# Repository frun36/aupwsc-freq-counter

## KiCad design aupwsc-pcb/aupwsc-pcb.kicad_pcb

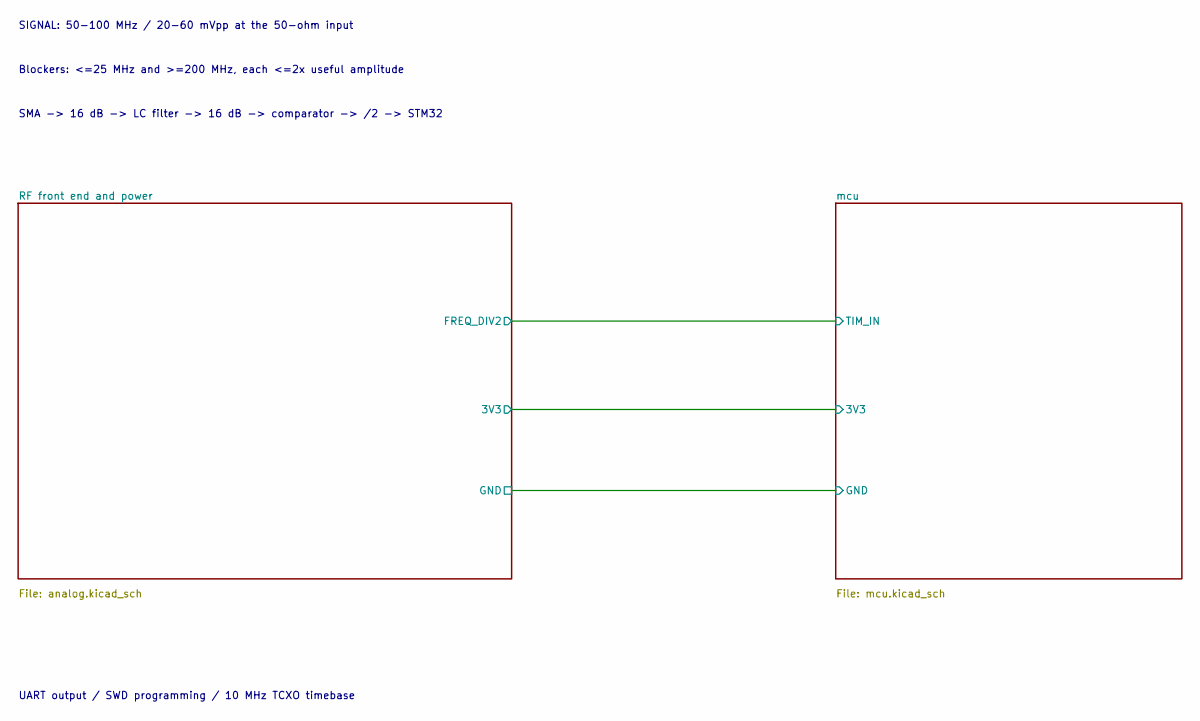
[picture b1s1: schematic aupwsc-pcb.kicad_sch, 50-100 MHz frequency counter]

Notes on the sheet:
UART output / SWD programming / 10 MHz TCXO timebase
SIGNAL: 50-100 MHz / 20-60 mVpp at the 50-ohm input
SMA -> 16 dB -> LC filter -> 16 dB -> comparator -> /2 -> STM32
Blockers: <=25 MHz and >=200 MHz, each <=2x useful amplitude

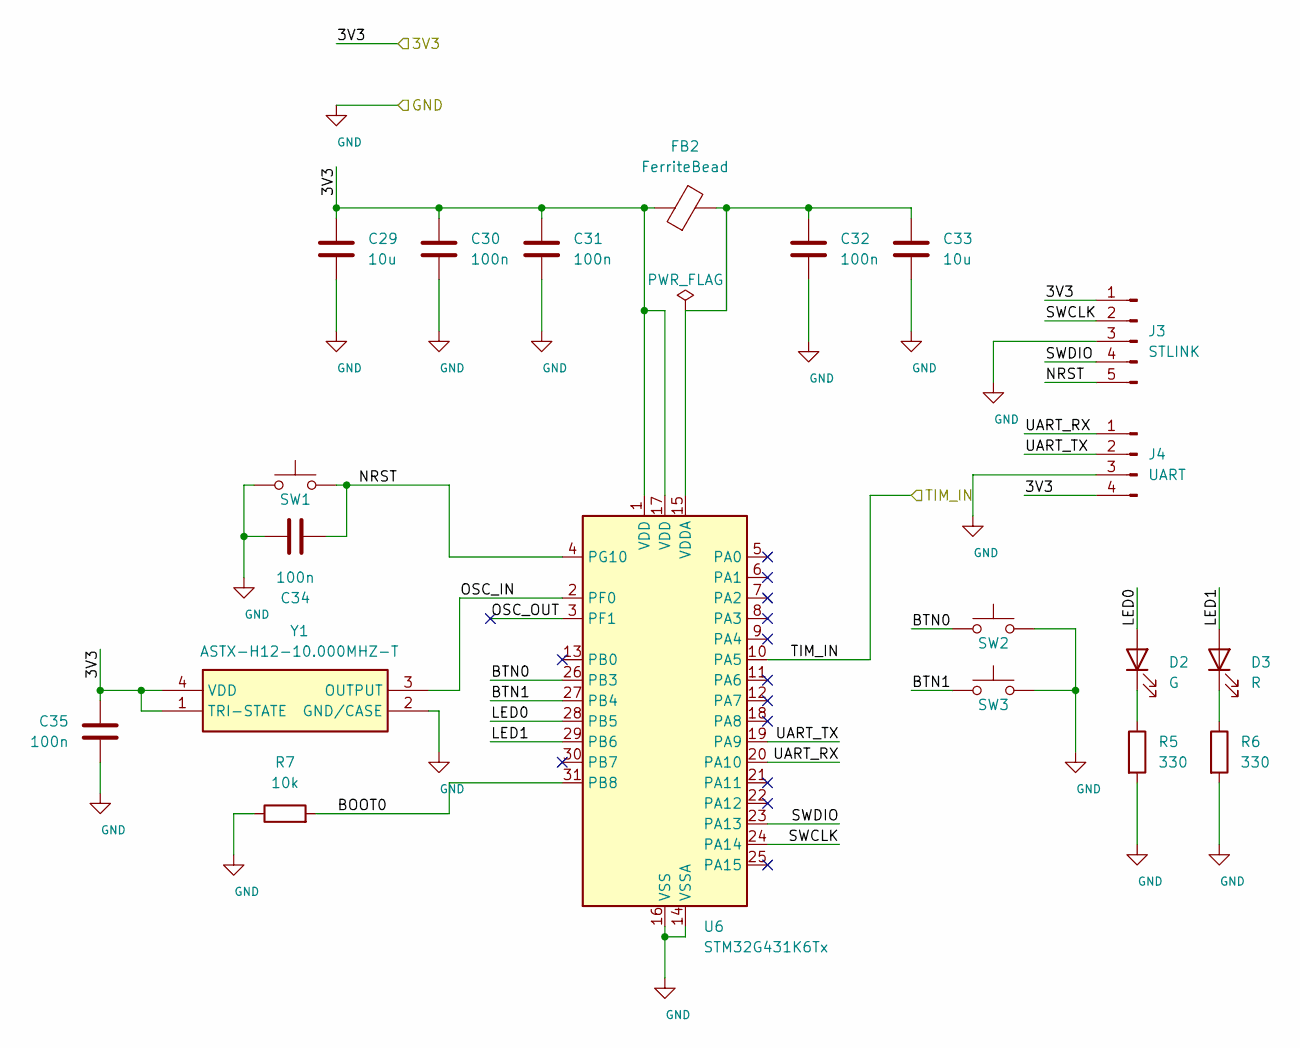
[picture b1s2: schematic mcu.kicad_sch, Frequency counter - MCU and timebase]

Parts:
C29, C33: 10u; C_0805_2012Metric_Pad1.18x1.45mm_HandSolder; MPN C0805C106K8RACAUTO
C30, C31, C32, C34, C35: 100n; C_0603_1608Metric_Pad1.08x0.95mm_HandSolder; MPN GRM188R71H104KA93D
D2: G; LED_0805_2012Metric_Pad1.15x1.40mm_HandSolder; MPN APT2012CGCK
D3: R; LED_0805_2012Metric_Pad1.15x1.40mm_HandSolder; MPN APT2012EC
FB2: FerriteBead; L_0603_1608Metric_Pad1.05x0.95mm_HandSolder; MPN BLM18AG601SN1D
J3: STLINK; PinHeader_1x05_P2.54mm_Vertical; MPN M20-9990545
J4: UART; PinHeader_1x04_P2.54mm_Vertical; MPN M20-9990445
R5, R6: 330; R_0603_1608Metric_Pad0.98x0.95mm_HandSolder; MPN RC0603FR-07330RL
R7: 10k; R_0603_1608Metric_Pad0.98x0.95mm_HandSolder; MPN RC0603FR-0710KL
SW1, SW2, SW3: SW_Push; SW_PUSH_6mm; MPN B3F-1000
U6: STM32G431K6Tx; LQFP-32_7x7mm_P0.8mm; MPN STM32G431K6T6
Y1: ASTX-H12-10.000MHZ-T; ASTX-H12; Mouser Part Number 815-ASTXH1210T

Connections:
/RF front end and power/3V3: C29.1, C30.1, C31.1, C35.1, FB2.1, J3.1, J4.4, U6.1 (VDD), U6.17 (VDD), Y1.1 (TRI-STATE), Y1.4 (VDD); also elsewhere on the board
/RF front end and power/FREQ_DIV2: U6.10 (PA5); also elsewhere on the board
/mcu/BOOT0: R7.2, U6.31 (PB8)
/mcu/BTN0: SW2.1, U6.26 (PB3)
/mcu/BTN1: SW3.1, U6.27 (PB4)
/mcu/LED0: D2.2 (A), U6.28 (PB5)
/mcu/LED1: D3.2 (A), U6.29 (PB6)
/mcu/NRST: C34.2, J3.5, SW1.2, U6.4 (PG10)
/mcu/OSC_IN: U6.2 (PF0), Y1.3 (OUTPUT)
/mcu/OSC_OUT: U6.3 (PF1)
/mcu/SWCLK: J3.2, U6.24 (PA14)
/mcu/SWDIO: J3.4, U6.23 (PA13)
/mcu/UART_RX: J4.1, U6.20 (PA10)
/mcu/UART_TX: J4.2, U6.19 (PA9)
GND: C29.2, C30.2, C31.2, C32.2, C33.2, C34.1, C35.2, J3.3, J4.3, R5.2, R6.2, R7.1, SW1.1, SW2.2, SW3.2, U6.14 (VSSA), U6.16 (VSS), U6.32 (VSS), Y1.2 (GND/CASE); also elsewhere on the board
unnamed: D2.1 (K), R5.1
unnamed: D3.1 (K), R6.1
unnamed: C32.1, C33.1, FB2.2, U6.15 (VDDA)

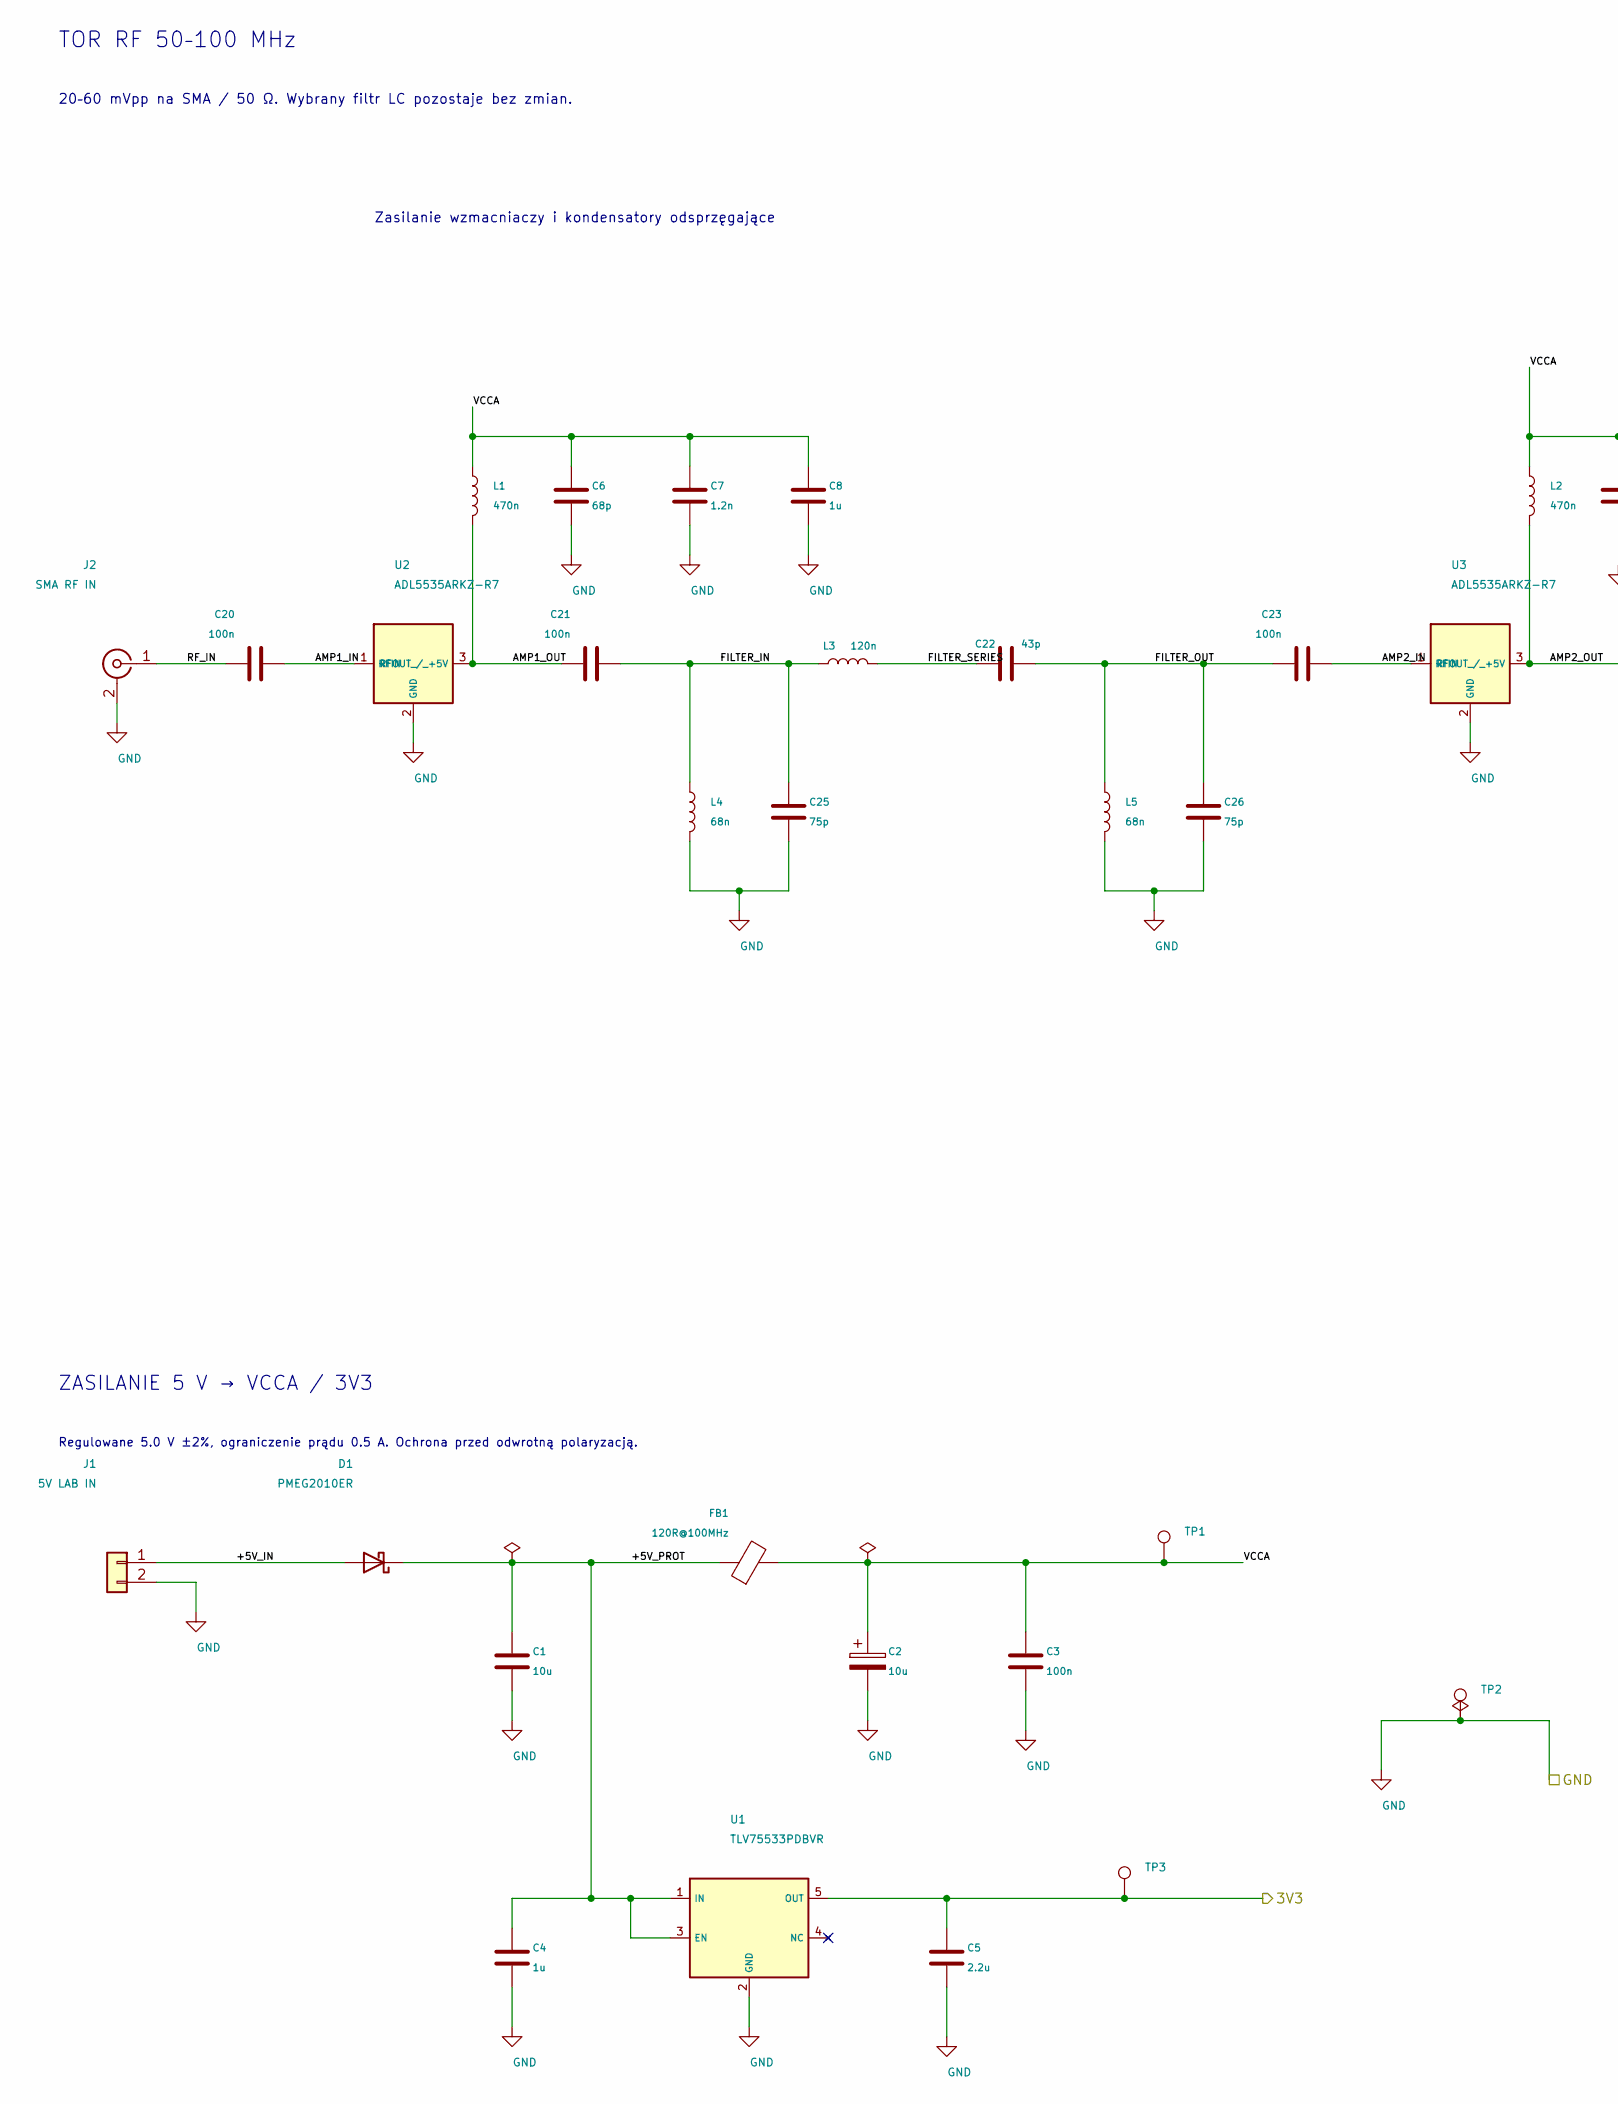
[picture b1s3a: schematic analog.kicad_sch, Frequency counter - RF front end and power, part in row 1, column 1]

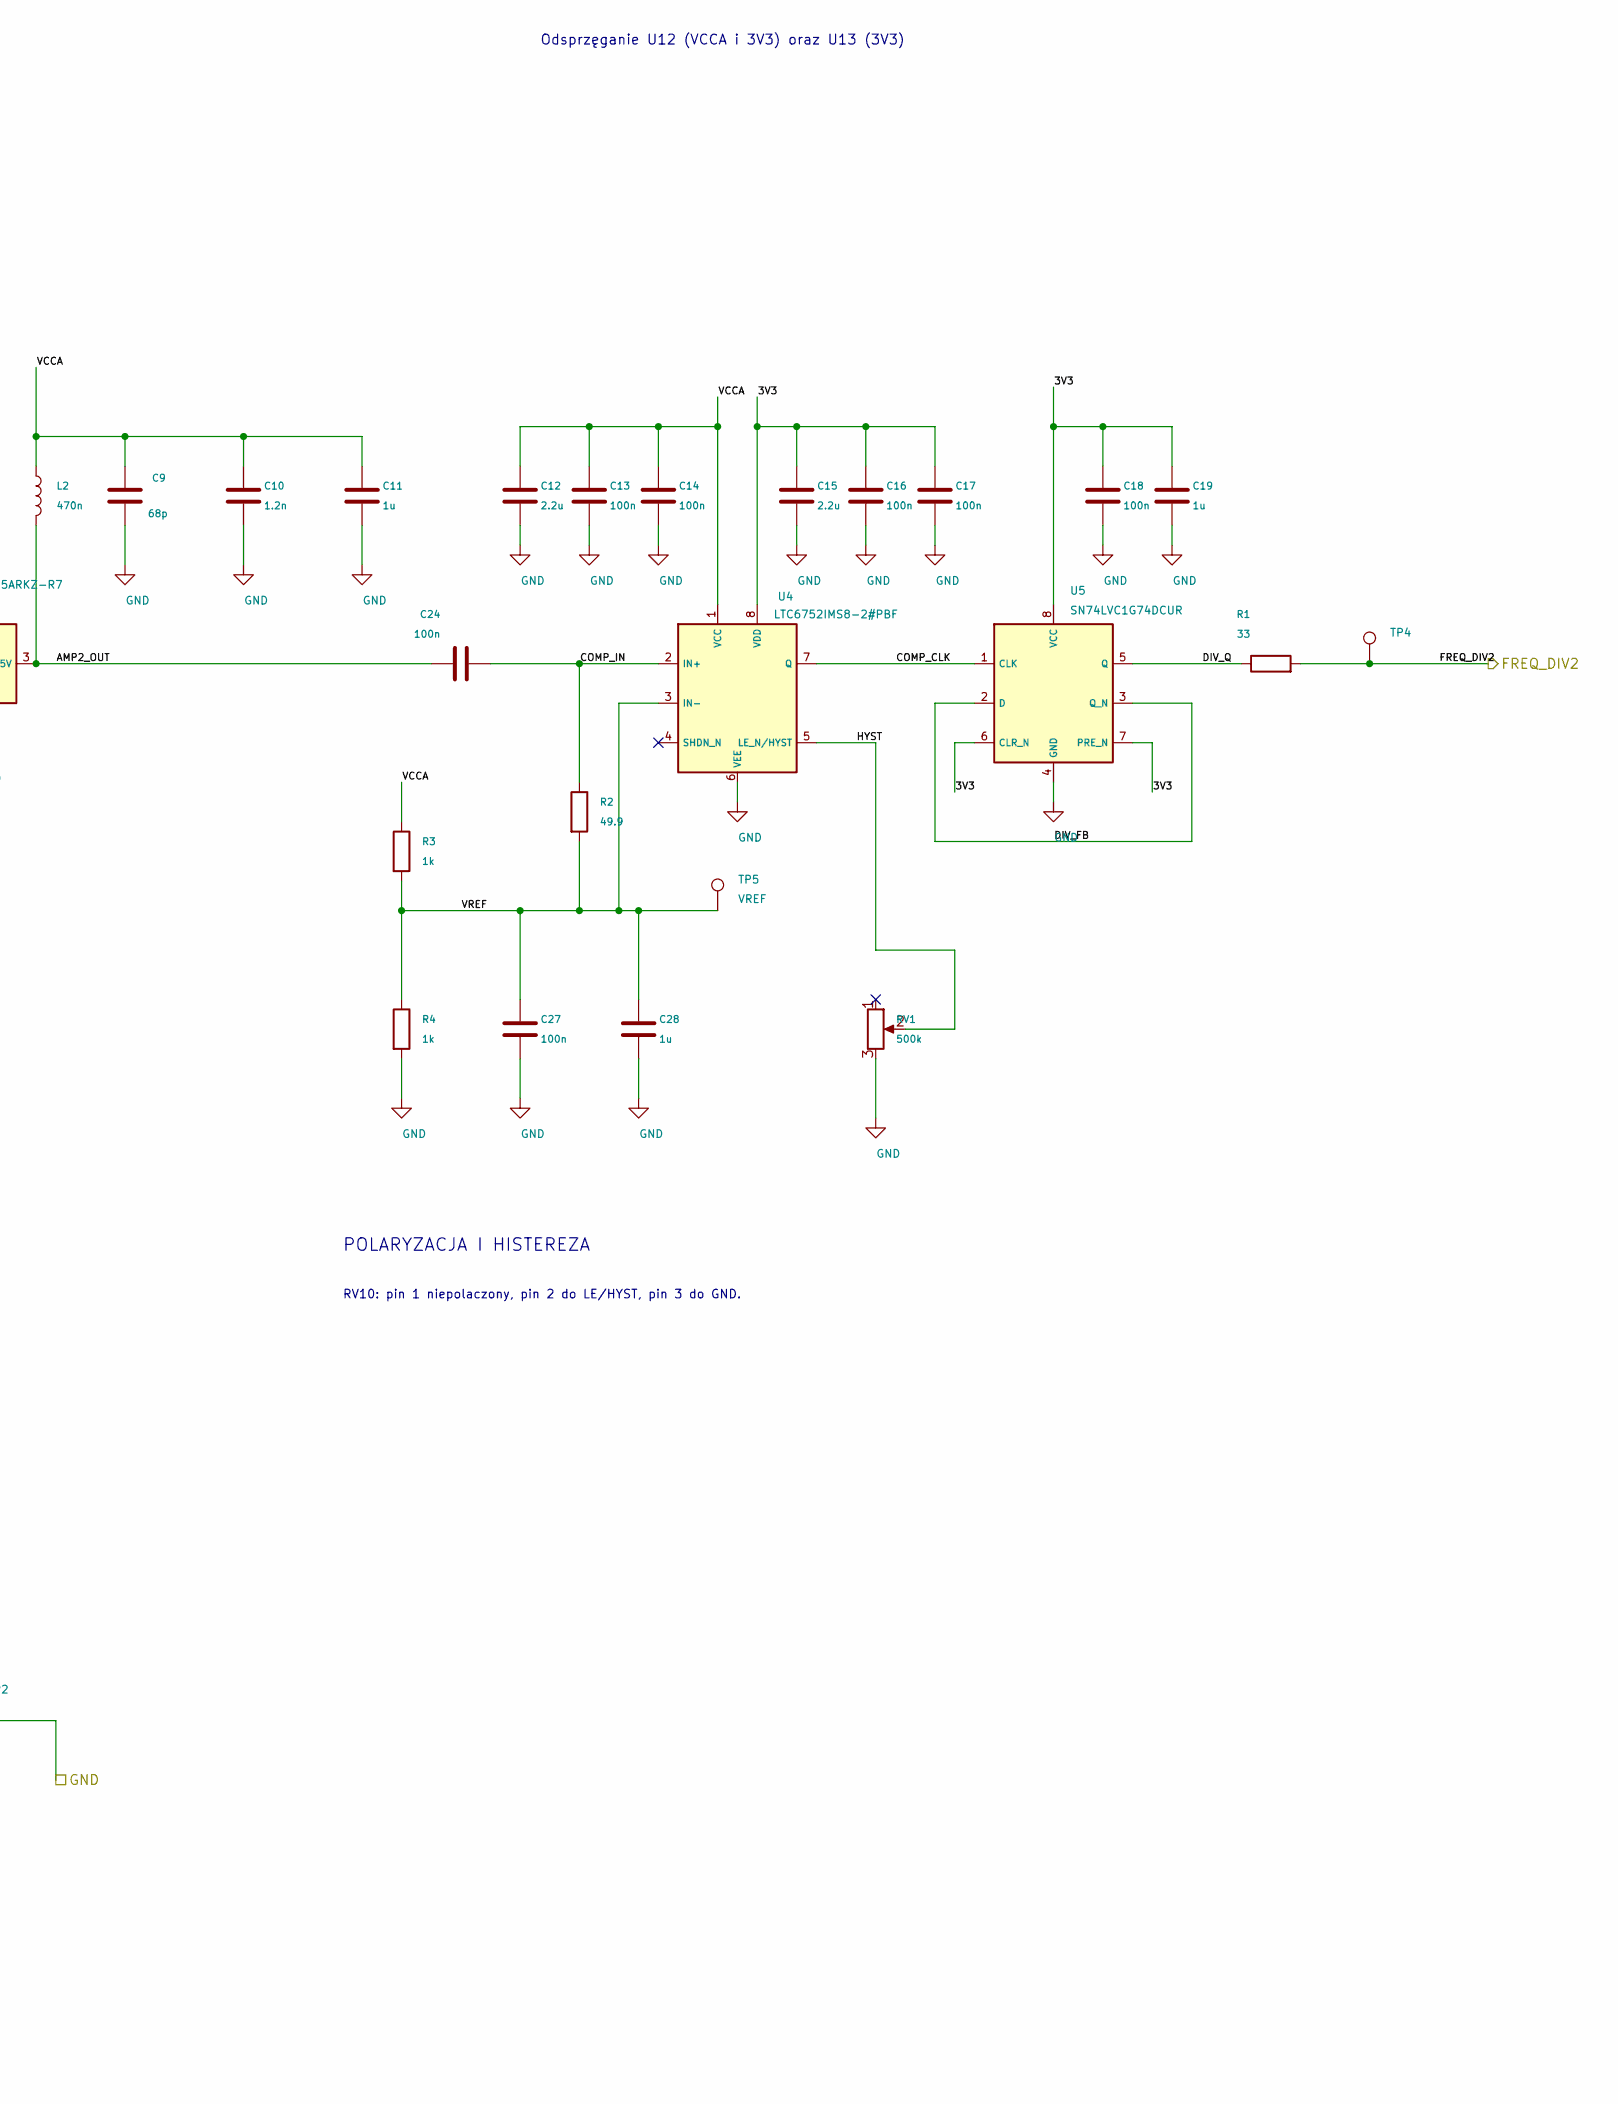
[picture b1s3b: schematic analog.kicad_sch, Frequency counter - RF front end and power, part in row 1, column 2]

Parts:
C1: 10u; C_0805_2012Metric; MPN C0805C106K8RACAUTO
C2: 10u; CP_EIA-3216-18_Kemet-A; MPN T491A106M016AT
C3, C13, C14, C16, C17, C18, C20, C21, C23, C24, C27: 100n; C_0603_1608Metric; MPN GRM188R71H104KA93D
C4, C8, C11, C19, C28: 1u; C_0603_1608Metric; MPN GRM188R61A105KA61D
C5, C12, C15: 2.2u; C_0805_2012Metric; MPN GRM21BR71C225KA12L
C6, C9: 68p; C_0603_1608Metric; MPN GCM1885C2A680JA16D
C7, C10: 1.2n; C_0603_1608Metric; MPN C1608C0G2A122J080AA
C22: 43p; C_0402_1005Metric_Pad0.74x0.62mm_HandSolder; MPN GCM1555C1H430FA16D
C25, C26: 75p; C_0402_1005Metric_Pad0.74x0.62mm_HandSolder; MPN GCM1555C1H750FA16D
D1: PMEG2010ER; Nexperia_CFP3_SOD-123W; MPN PMEG2010ER,115
FB1: 120R@100MHz; L_1206_3216Metric; MPN BLM31PG121SN1L
J1: 5V LAB IN; TerminalBlock_Phoenix_MKDS-1,5-2-5.08_1x02_P5.08mm_Horizont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; MPN 1715721
J2: SMA RF IN; SMA_Amphenol_132203-12_Horizontal; MPN 132203-12
L1, L2: 470n; L_0603_1608Metric; MPN LQW18CNR47J00D
L3: 120n; L_0603_1608Metric; MPN LQW18ANR12G00D
L4, L5: 68n; L_0603_1608Metric; MPN LQW18AN68NG00D
R1: 33; R_0603_1608Metric; MPN RC0603FR-0733RL
R2: 49.9; R_0603_1608Metric; MPN WR06X49R9FTL
R3, R4: 1k; R_0603_1608Metric; MPN RC0603FR-071KL
RV1: 500k; Potentiometer_Bourns_3296W_Vertical; MPN 3296W-1-504LF
TP1: VCCA; TestPoint_Pad_D1.5mm; MPN PCB_PAD_ONLY
TP2: GND; TestPoint_Pad_D1.5mm; MPN PCB_PAD_ONLY
TP3: 3V3; TestPoint_Pad_D1.5mm; MPN PCB_PAD_ONLY
TP4: FREQ_DIV2; TestPoint_Pad_D1.5mm; MPN PCB_PAD_ONLY
TP5: VREF; TestPoint_Pad_D1.5mm; MPN PCB_PAD_ONLY
U1: TLV75533PDBVR; SOT-23-5; MPN TLV75533PDBVR
U2, U3: ADL5535ARKZ-R7; SOT-89-3; MPN ADL5535ARKZ-R7
U4: LTC6752IMS8-2#PBF; MSOP-8_3x3mm_P0.65mm; MPN LTC6752IMS8-2#PBF
U5: SN74LVC1G74DCUR; VSSOP-8_2.3x2mm_P0.5mm; MPN SN74LVC1G74DCUR

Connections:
/RF front end and power/3V3: C5.1, C15.1, C16.1, C17.1, C18.1, C19.1, TP3.1 (1_1), U1.5 (OUT), U4.8 (VDD), U5.6 (CLR_N), U5.7 (PRE_N), U5.8 (VCC); also elsewhere on the board
/RF front end and power/+5V_IN: D1.2 (A), J1.1
/RF front end and power/+5V_PROT: C1.1, C4.1, D1.1 (K), FB1.1, U1.1 (IN), U1.3 (EN)
/RF front end and power/AMP1_IN: C20.2, U2.1 (RFIN)
/RF front end and power/AMP1_OUT: C21.1, L1.2, U2.3 (RFOUT_/_+5V)
/RF front end and power/AMP2_IN: C23.2, U3.1 (RFIN)
/RF front end and power/AMP2_OUT: C24.1, L2.2, U3.3 (RFOUT_/_+5V)
/RF front end and power/COMP_CLK: U4.7 (Q), U5.1 (CLK)
/RF front end and power/COMP_IN: C24.2, R2.1, U4.2 (IN+)
/RF front end and power/DIV_FB: U5.2 (D), U5.3 (Q_N)
/RF front end and power/DIV_Q: R1.1, U5.5 (Q)
/RF front end and power/FILTER_IN: C21.2, C25.1, L3.1, L4.1
/RF front end and power/FILTER_OUT: C22.2, C23.1, C26.1, L5.1
/RF front end and power/FILTER_SERIES: C22.1, L3.2
/RF front end and power/FREQ_DIV2: R1.2, TP4.1 (1_1); also elsewhere on the board
/RF front end and power/HYST: RV1.2, U4.5 (LE_N/HYST)
/RF front end and power/RF_IN: C20.1, J2.1 (In)
/RF front end and power/VCCA: C2.1, C3.1, C6.1, C7.1, C8.1, C9.1, C10.1, C11.1, C12.1, C13.1, C14.1, FB1.2, L1.1, L2.1, R3.1, TP1.1 (1_1), U4.1 (VCC)
/RF front end and power/VREF: C27.1, C28.1, R2.2, R3.2, R4.1, TP5.1 (1_1), U4.3 (IN-)
GND: C1.2, C2.2, C3.2, C4.2, C5.2, C6.2, C7.2, C8.2, C9.2, C10.2, C11.2, C12.2, C13.2, C14.2, C15.2, C16.2, C17.2, C18.2, C19.2, C25.2, C26.2, C27.2, C28.2, J1.2, J2.2 (Ext), L4.2, L5.2, R4.2, RV1.3, TP2.1 (1_1), U1.2 (GND), U2.2 (GND), U3.2 (GND), U4.6 (VEE), U5.4 (GND); also elsewhere on the board

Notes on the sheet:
Regulowane 5.0 V ±2%, ograniczenie prądu 0.5 A. Ochrona przed odwrotną polaryzacją.
ZASILANIE 5 V → VCCA / 3V3
POLARYZACJA I HISTEREZA
RV10: pin 1 niepolaczony, pin 2 do LE/HYST, pin 3 do GND.
20–60 mVpp na SMA / 50 Ω. Wybrany filtr LC pozostaje bez zmian.
TOR RF 50–100 MHz
Zasilanie wzmacniaczy i kondensatory odsprzęgające
Odsprzęganie U12 (VCCA i 3V3) oraz U13 (3V3)

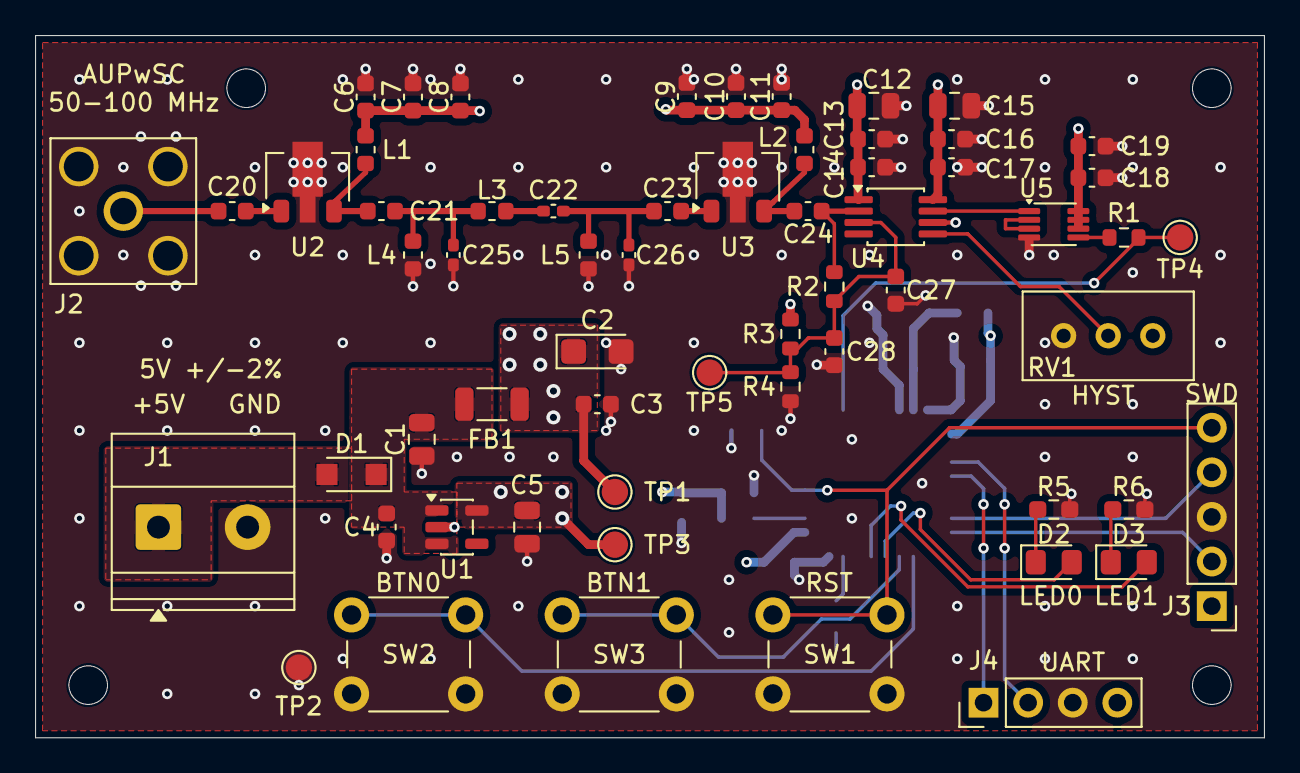
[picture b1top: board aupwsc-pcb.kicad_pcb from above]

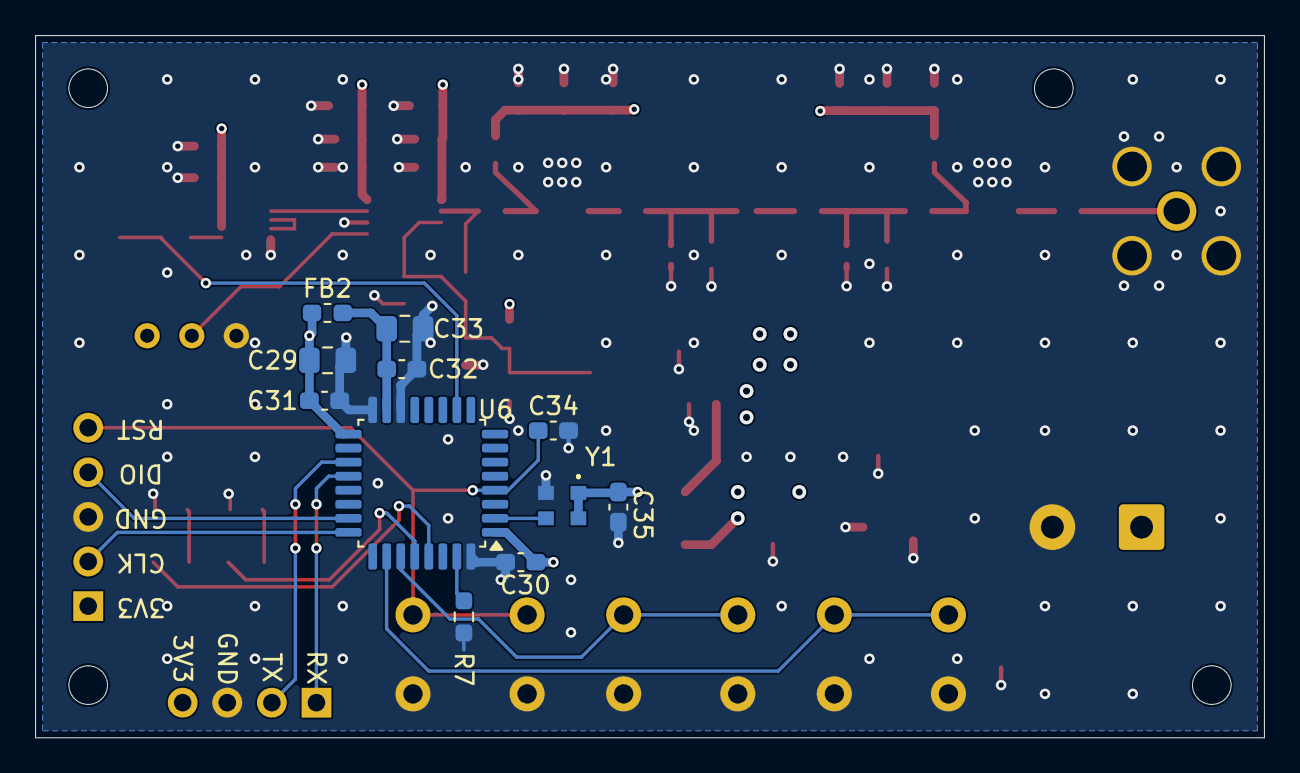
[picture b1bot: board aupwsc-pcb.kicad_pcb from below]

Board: 4 copper layers, 70.0 x 40.0 mm, 76 parts (11 on the bottom side), 34 nets.

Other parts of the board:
H1, H2, H3, H4: M2; MountingHole_2.2mm_M2

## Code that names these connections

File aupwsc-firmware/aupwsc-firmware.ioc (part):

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Mcu.Name=STM32G431K(6-8-B)Tx
Mcu.Package=LQFP32
Mcu.UserName=STM32G431K6Tx
PA10.Mode=Asynchronous
PA10.Signal=USART1_RX
PA13.Mode=Serial_Wire
PA13.Signal=SYS_JTMS-SWDIO
PA14.Mode=Serial_Wire
PA14.Signal=SYS_JTCK-SWCLK
PA5.GPIOParameters=GPIO_Speed
PA5.GPIO_Speed=GPIO_SPEED_FREQ_VERY_HIGH
PA5.Signal=S_TIM2_ETR
PA9.Mode=Asynchronous
PA9.Signal=USART1_TX
PB3.GPIOParameters=GPIO_Label
PB3.GPIO_Label=BTN0
PB3.Signal=GPIO_Input
PB4.GPIOParameters=GPIO_Label
PB4.GPIO_Label=BTN1
PB4.Signal=GPIO_Input
PB5.GPIOParameters=GPIO_Label
PB5.GPIO_Label=LED0
PB5.Signal=GPIO_Output
PB6.GPIOParameters=GPIO_Label
PB6.GPIO_Label=LED1
PB6.Signal=GPIO_Output
PF0-OSC_IN.Mode=HSE-External-Clock-Source
PF0-OSC_IN.Signal=RCC_OSC_IN
RCC.HSE_VALUE=10000000
RCC.SYSCLKFreq_VALUE=170000000
RCC.SYSCLKSource=RCC_SYSCLKSOURCE_PLLCLK
board=custom
